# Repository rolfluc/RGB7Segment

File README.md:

# RGB7Segment
Board for 7 Segment, based on some variant of the NeoPixel

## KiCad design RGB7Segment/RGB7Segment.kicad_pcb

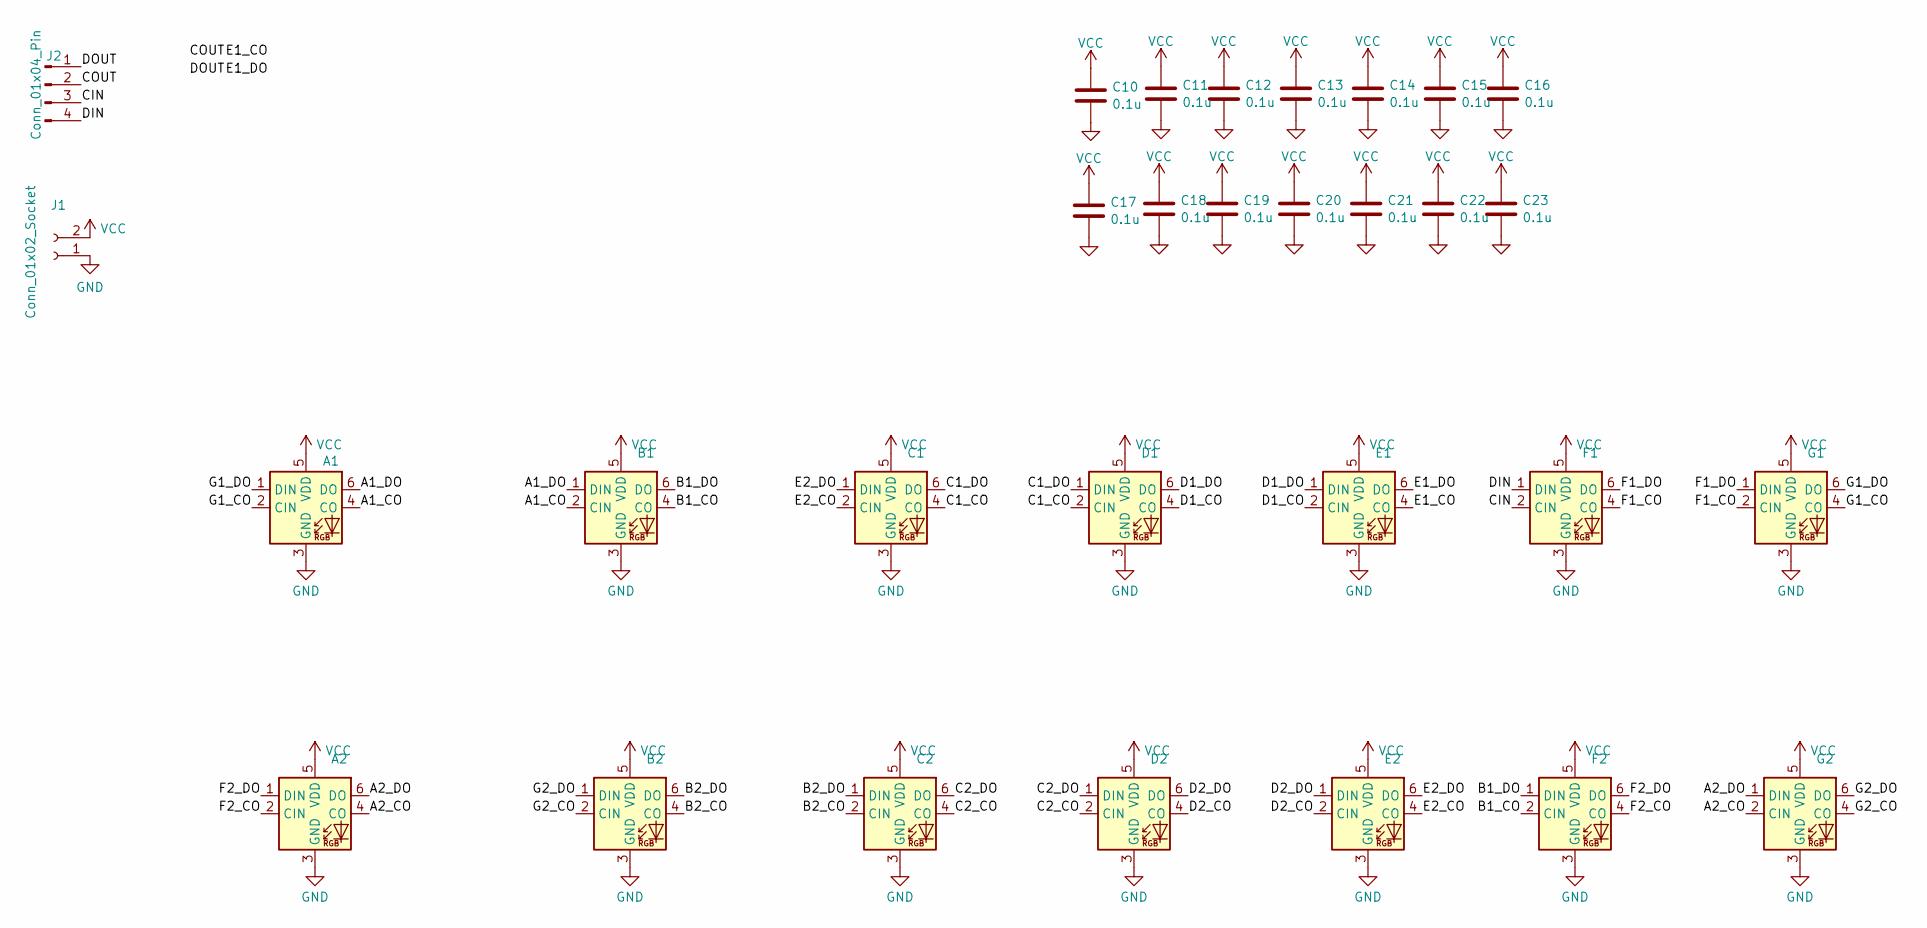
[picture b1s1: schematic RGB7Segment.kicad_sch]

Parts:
A1, A2: 587-2086-247F
B1, B2: 587-2086-247F
C1, C2: 587-2086-247F
C10, C11, C12, C13, C14, C15, C16, C17, C18, C19, C20, C21, C22, C23: 0.1u; C_0402_1005Metric
D1, D2: 587-2086-247F
E1, E2: 587-2086-247F
F1, F2: 587-2086-247F
G1, G2: 587-2086-247F
J1: Conn_01x02_Socket; PinHeader_1x02_P1.27mm_Vertical
J2: Conn_01x04_Pin; PinHeader_1x04_P1.27mm_Vertical

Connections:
/A1_CO: A1.4 (CO), B1.2 (CIN)
/A1_DO: A1.6 (DO), B1.1 (DIN)
/A2_CO: A2.4 (CO), G2.2 (CIN)
/A2_DO: A2.6 (DO), G2.1 (DIN)
/B1_CO: B1.4 (CO), F2.2 (CIN)
/B1_DO: B1.6 (DO), F2.1 (DIN)
/B2_CO: B2.4 (CO), C2.2 (CIN)
/B2_DO: B2.6 (DO), C2.1 (DIN)
/C1_CO: C1.4 (CO), D1.2 (CIN)
/C1_DO: C1.6 (DO), D1.1 (DIN)
/C2_CO: C2.4 (CO), D2.2 (CIN)
/C2_DO: C2.6 (DO), D2.1 (DIN)
/CIN: F1.2 (CIN), J2.3; also elsewhere on the board
/COUT: E1.4 (CO), J2.2; also elsewhere on the board
/D1_CO: D1.4 (CO), E1.2 (CIN)
/D1_DO: D1.6 (DO), E1.1 (DIN)
/D2_CO: D2.4 (CO), E2.2 (CIN)
/D2_DO: D2.6 (DO), E2.1 (DIN)
/DIN: F1.1 (DIN), J2.4; also elsewhere on the board
/DOUT: E1.6 (DO), J2.1; also elsewhere on the board
/E2_CO: C1.2 (CIN), E2.4 (CO)
/E2_DO: C1.1 (DIN), E2.6 (DO)
/F1_CO: F1.4 (CO), G1.2 (CIN)
/F1_DO: F1.6 (DO), G1.1 (DIN)
/F2_CO: A2.2 (CIN), F2.4 (CO)
/F2_DO: A2.1 (DIN), F2.6 (DO)
/G1_CO: A1.2 (CIN), G1.4 (CO)
/G1_DO: A1.1 (DIN), G1.6 (DO)
/G2_CO: B2.2 (CIN), G2.4 (CO)
/G2_DO: B2.1 (DIN), G2.6 (DO)
GND: A1.3 (GND), A2.3 (GND), B1.3 (GND), B2.3 (GND), C1.3 (GND), C2.3 (GND), C10.2, C11.2, C12.2, C13.2, C14.2, C15.2, C16.2, C17.2, C18.2, C19.2, C20.2, C21.2, C22.2, C23.2, D1.3 (GND), D2.3 (GND), E1.3 (GND), E2.3 (GND), F1.3 (GND), F2.3 (GND), G1.3 (GND), G2.3 (GND), J1.1; also elsewhere on the board
VCC: A1.5 (VDD), A2.5 (VDD), B1.5 (VDD), B2.5 (VDD), C1.5 (VDD), C2.5 (VDD), C10.1, C11.1, C12.1, C13.1, C14.1, C15.1, C16.1, C17.1, C18.1, C19.1, C20.1, C21.1, C22.1, C23.1, D1.5 (VDD), D2.5 (VDD), E1.5 (VDD), E2.5 (VDD), F1.5 (VDD), F2.5 (VDD), G1.5 (VDD), G2.5 (VDD), J1.2; also elsewhere on the board

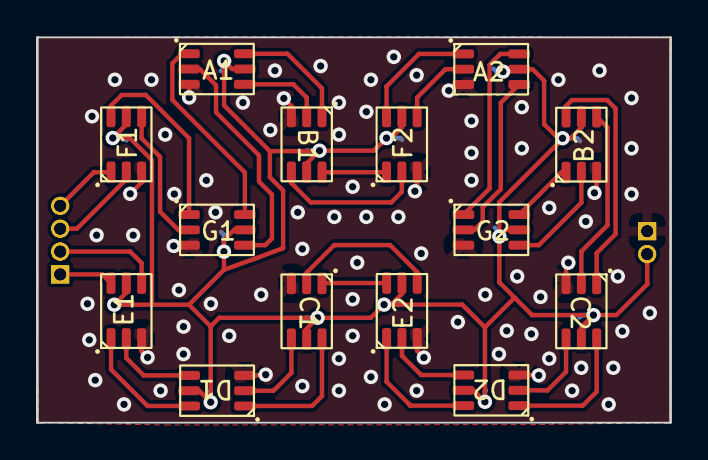
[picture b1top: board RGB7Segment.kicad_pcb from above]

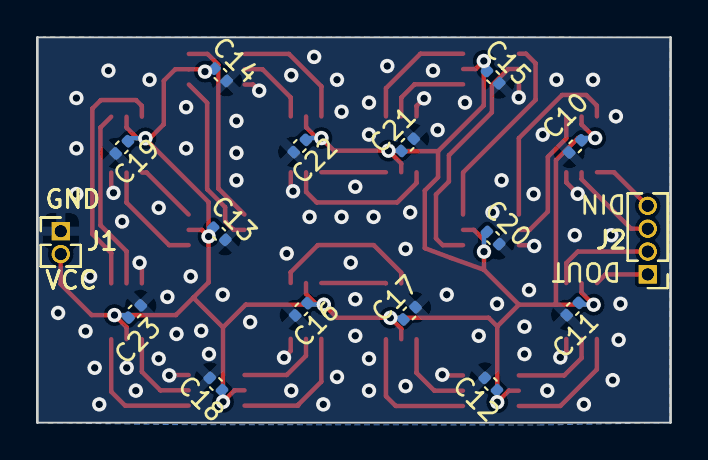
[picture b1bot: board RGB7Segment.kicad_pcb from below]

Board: 2 copper layers, 35.2 x 21.4 mm, 32 parts (18 on the bottom side), 32 nets.

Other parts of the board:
J1#2: Conn_01x02_Socket; PinHeader_1x02_P1.27mm_Vertical
J2#2: Conn_01x04_Pin; PinHeader_1x04_P1.27mm_Vertical

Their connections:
/CIN: J2#2.3; also elsewhere on the board
/COUT: J2#2.2; also elsewhere on the board
/DIN: J2#2.4; also elsewhere on the board
/DOUT: J2#2.1; also elsewhere on the board
GND: J1#2.1; also elsewhere on the board
VCC: J1#2.2; also elsewhere on the board

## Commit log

2024-10-06 Sample Board Ordered, setup defined.
2024-10-07 Slotted/Cut Design Uploaded. Waiting on COnfirmation of Operation
2024-10-11 Small RGB 7 Segment with cutout
2024-10-13 Moving Design over to non cutout.
2024-10-16 Cleaning up PCB, and minor cleanup.
2024-10-20 Adding New Models,
2024-10-20 Smaller Size first pass layout
2024-10-21 New Pass of RGB 7 Segment
2024-10-23 Rev out to mfger
2024-10-27 Adding first SW control for
2024-10-27 Adding Untested SPI DMA Driver
2024-10-27 Potentially working LED Filler
2024-10-27 WIP Segment Interface
2024-10-27 First pass Display Driver implementation
2024-10-27 Untested Driver, doing sample data transfer.
2024-11-03 Minor Footprint mod. Need to change PCB still
2024-11-03 Updated SPI/DMA Controller Not Faulting but not working
2024-11-03 Potentially working SPI Waveform
2024-11-09 Potentially revamp to PWM driver instead of SPI
2024-11-09 Potential move over to PWM from SPI
2024-11-09 PWM Toggles Pin, Clock appears broken
2024-11-10 Reverted Changes to Sysclock Changes
2024-11-10 Partly working PWM
    Pulse Timing appears wrong, but PWM output is sending out correct number
    of pulses
2024-11-11 Working PWM
    PWM is working correctly, just runs once due to timer issues.
2024-11-23 Properly timed 4 words
    4 words properly alternating between high/low bits.
    Second execution doesn't appear to load correctly
2024-11-23 Fixed Timing. Now is repeatable.
2024-11-23 Timing More easily calculated
2024-11-23 Timing appears working, weird artifacts after
2024-11-23 Working Display Driver - According to timing
2024-11-24 Working LED!
2024-11-24 Smaller Footprint, removed all traces, pre-re-layout
2024-11-24 New Layout possibility
2024-11-25 new board, shipped to mfging,
2025-01-13 Not Working PWM. Fights with either > 80% and < 30%.
    Need to switch back to SPI. PWM driver does not work for both sides of
    getting close to 75%, and 25% within the same code. and use DMA. SPI at
    least will hopefully be able to provide less data consumption as well
2025-01-14 Close to proper timing, minor cleanup
2025-01-17 Adding base parts / positioning.
    Needs further alignment for horizontal vs Verticle SKU
2025-01-17 Adding Project Setup
2025-01-17 Standard push of SW in progress
2025-01-17 Initial Horizontal Placement
2025-01-17 Submitted RGB 7 Segment Layout
2025-01-19 Potential working sol'n for horizontal
2025-02-01 Working 7 Segment Layout
2025-02-14 Slightly better spaced layout
2025-03-25 New Layout for diffuser. Needs further direction.
2025-03-25 New Minor Layout
2025-03-25 New Layout and placement of parts.
2025-03-25 Routing Complete
2025-03-25 Adding Vias
2025-03-26 Ordered Board
